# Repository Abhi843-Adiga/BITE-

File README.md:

Bite Force Measurement Device:  
A project for a portable, ESP32-based device designed to measure bite force, intended for wellness and bio-feedback applications.

Project Overview : 

->This open-source project provides the hardware foundation for a handheld device that measures bite force using a Flexiforce sensor.   
->The data is processed by an ESP32-C3 MCU and displayed in real-time on an SPI screen.  
->The device is designed to be a portable, battery-powered,rechargable tool for non-medical, wellness-related bio-feedback and personal data tracking.

Firmware:

This repository contains the hardware design only. The firmware needs to be developed separately using platforms like the ESP-IDF or the Arduino Core for ESP32.

Core firmware tasks would include:
1.  Reading analog values from the Flexiforce sensor via the MCP6004.
2.  Converting ADC values to force units (Newtons or lbs).
3.  Driving the SPI display to show real-time readings.

Design & Development Disclaimer:

1.Hardware Status:
These PCB designs are for prototyping purposes only.
Passed Checks:
The layouts have passed basic ERC (Electrical Rules Check) and DRC (Design Rule Check).

Untested Aspects:
The designs have not been validated for Signal Integrity (SI),Power Integrity (PI), or EMI/EMC.

They are not guaranteed to pass regulatory certifications without further analysis and revisions.

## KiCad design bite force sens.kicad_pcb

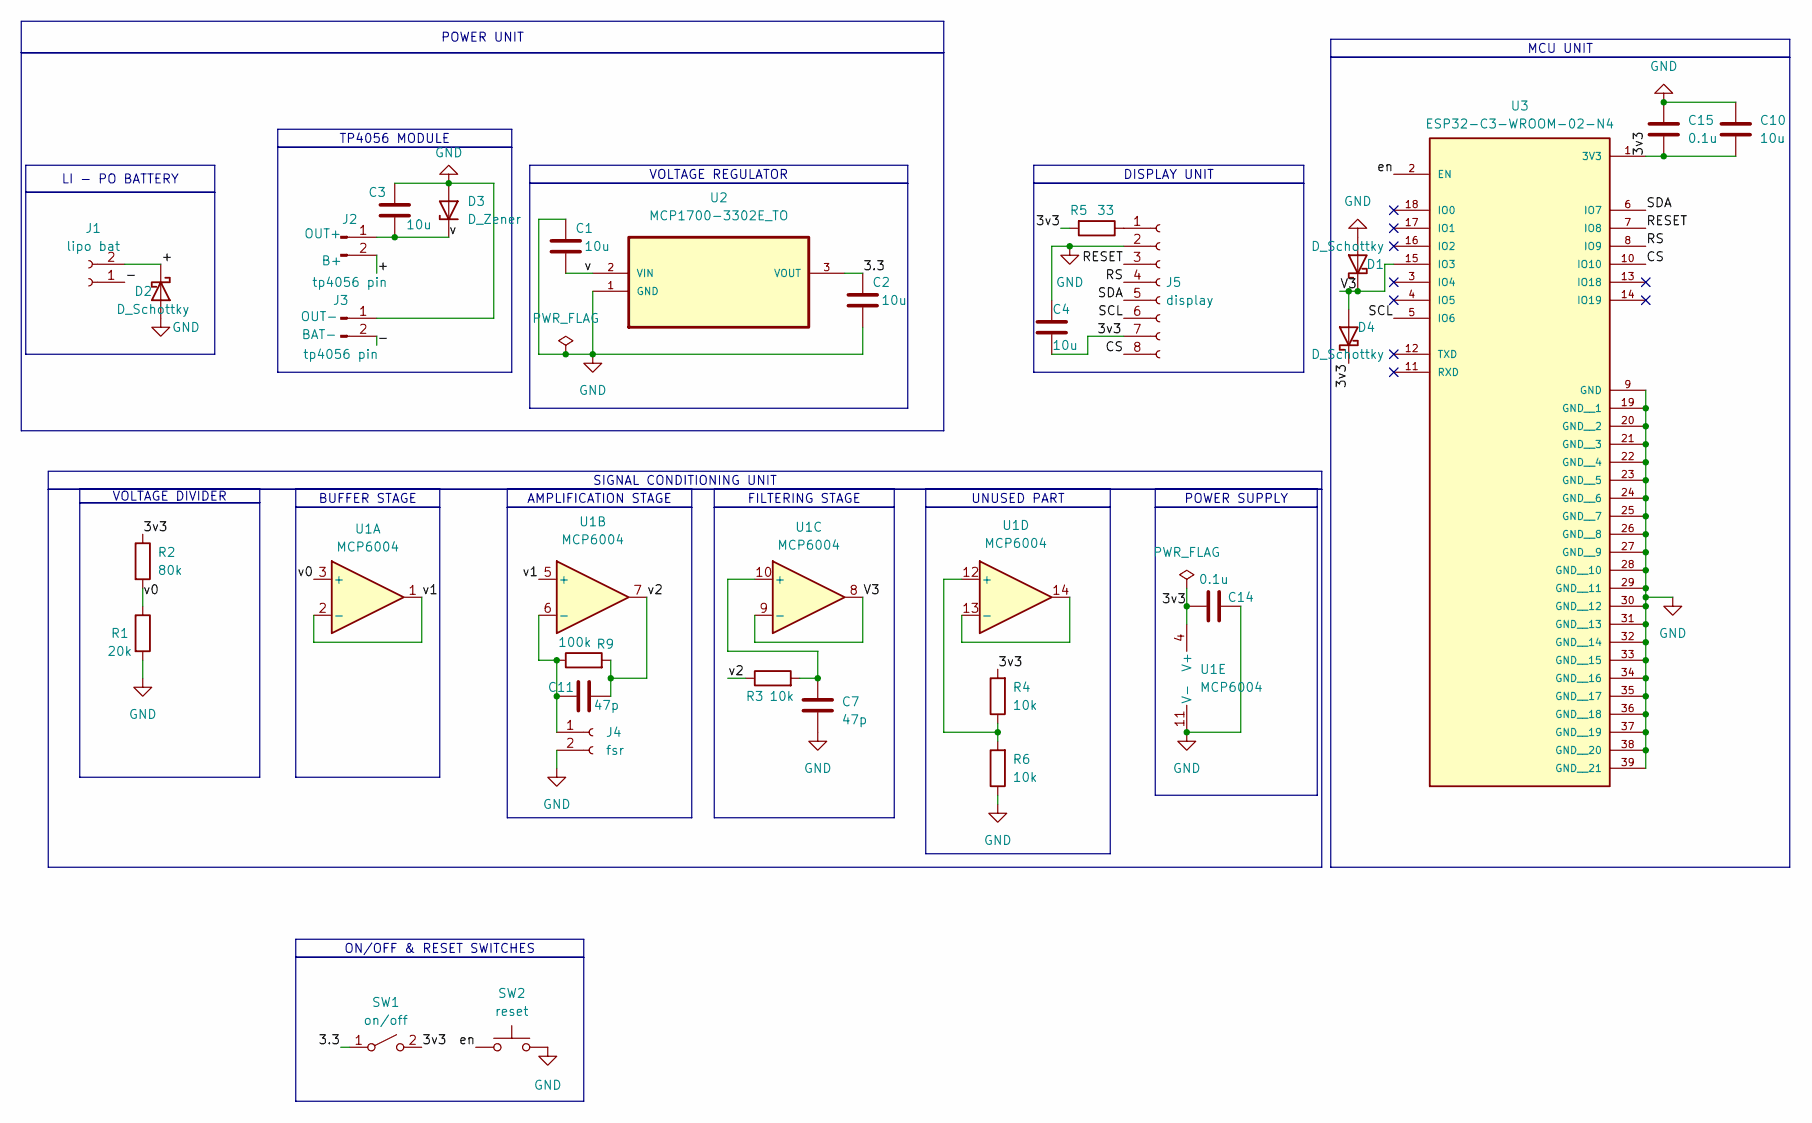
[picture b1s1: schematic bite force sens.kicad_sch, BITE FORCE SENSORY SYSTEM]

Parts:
C1, C2, C3, C4, C10: 10u; C_0805_2012Metric
C7, C11: 47p; C_0805_2012Metric
C14, C15: 0.1u; C_0805_2012Metric
D1, D2, D4: D_Schottky; D_SMA
D3: D_Zener; D_SMA
J1: lipo bat; JWT_A3963_1x02_P3.96mm_Vertical
J2, J3: tp4056 pin; PinHeader_1x02_P2.54mm_Vertical
J4: fsr; JST_PH_B2B-PH-K_1x02_P2.00mm_Vertical
J5: display; Hirose_FH12-8S-0.5SH_1x08-1MP_P0.50mm_Horizontal
R1: 20k; R_0805_2012Metric
R2: 80k; R_0805_2012Metric
R3, R4, R6: 10k; R_0805_2012Metric
R5: 33; R_0805_2012Metric
R9: 100k; R_0805_2012Metric
SW1: on/off; SW_DIP_SPSTx01_Slide_6.7x4.1mm_W6.73mm_P2.54mm_LowProfile_J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
SW2: reset; SW_PUSH_6mm
U1: MCP6004; SOIC-14_3.9x8.7mm_P1.27mm
U2: MCP1700-3302E_TO; TO127P254X495-3; MPN MCP1700-3302E/TO
U3: ESP32-C3-WROOM-02-N4; MODULE_ESP32-C3-WROOM-02-H4

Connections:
/3.3: C2.1, SW1.1 (A), U2.3 (VOUT)
/3v3: C4.2, C10.2, C14.1, C15.2, D4.1 (K), J5.7, R2.1, R4.2, R5.2, SW1.2 (B), U1.4 (V+), U3.1 (3V3)
/+: D2.1 (K), J1.2, J2.2
/-: J1.1, J3.2
/CS: J5.8, U3.10 (IO10)
/RESET: J5.3, U3.7 (IO8)
/RS: J5.4, U3.8 (IO9)
/SCL: J5.6, U3.5 (IO6)
/SDA: J5.5, U3.6 (IO7)
/V3: D1.1 (K), D4.2 (A), U1.8, U1.9 (-), U3.15 (IO3)
/en: SW2.1, U3.2 (EN)
/v: C1.2, C3.2, D3.1 (K), J2.1, U2.2 (VIN)
/v0: R1.1, R2.2, U1.3 (+)
/v1: U1.1, U1.2 (-), U1.5 (+)
/v2: C11.2, R3.1, R9.2, U1.7
GND: C1.1, C2.2, C3.1, C4.1, C7.2, C10.1, C14.2, C15.1, D1.2 (A), D2.2 (A), D3.2 (A), J3.1, J4.2, J5.2, R1.2, R6.1, SW2.2, U1.11 (V-), U2.1 (GND), U3.9 (GND), U3.19 (GND__1), U3.20 (GND__2), U3.21 (GND__3), U3.22 (GND__4), U3.23 (GND__5), U3.24 (GND__6), U3.25 (GND__7), U3.26 (GND__8), U3.27 (GND__9), U3.28 (GND__10), U3.29 (GND__11), U3.30 (GND__12), U3.31 (GND__13), U3.32 (GND__14), U3.33 (GND__15), U3.34 (GND__16), U3.35 (GND__17), U3.36 (GND__18), U3.37 (GND__19), U3.38 (GND__20), U3.39 (GND__21)
unnamed: C11.1, J4.1, R9.1, U1.6 (-)
unnamed: J5.1, R5.1
unnamed: C7.1, R3.2, U1.10 (+)
unnamed: R4.1, R6.2, U1.12 (+)
unnamed: U1.13 (-), U1.14

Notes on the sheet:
LI - PO BATTERY
POWER UNIT
MCU UNIT
TP4056 MODULE
UNUSED PART
FILTERING STAGE
DISPLAY UNIT
SIGNAL CONDITIONING UNIT
VOLTAGE REGULATOR
VOLTAGE DIVIDER
ON/OFF & RESET SWITCHES
POWER SUPPLY
BUFFER STAGE
AMPLIFICATION STAGE

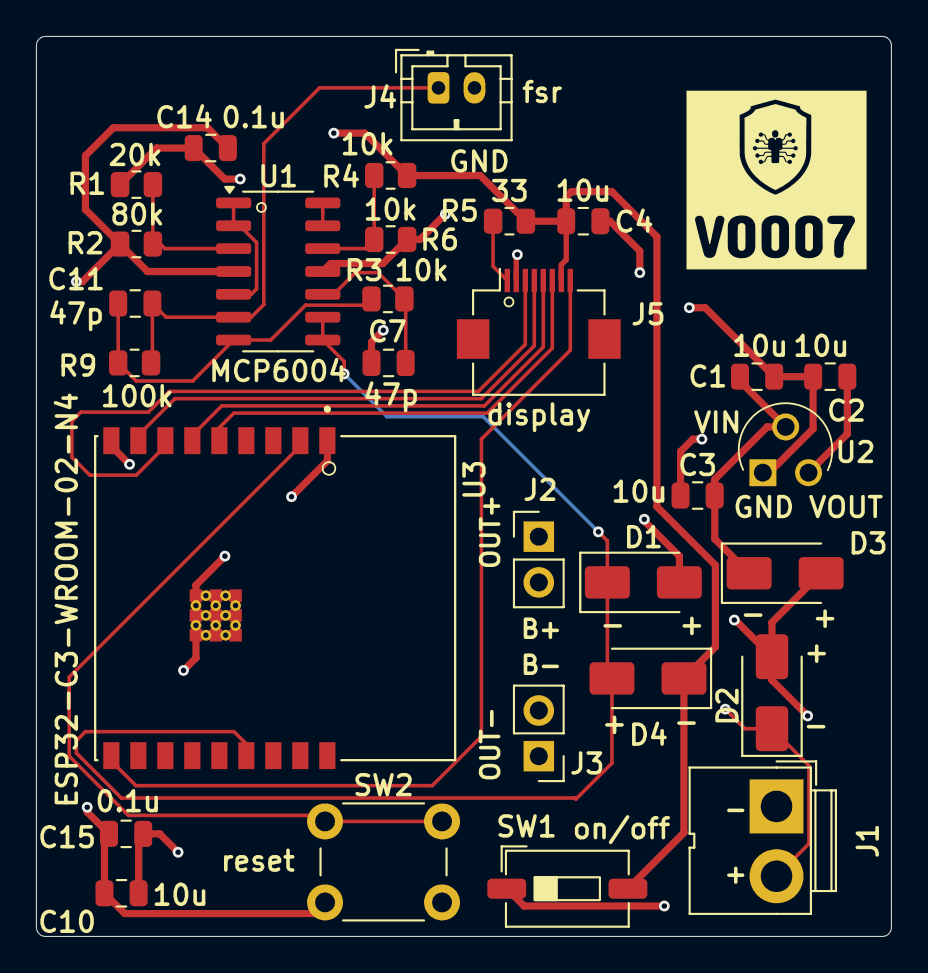
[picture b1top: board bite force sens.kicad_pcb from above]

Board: 4 copper layers, 47.5 x 50.0 mm, 30 parts (0 on the bottom side), 21 nets.

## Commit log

2025-06-18 added ressitor
2025-06-18 added ressitor again
2025-06-18 removed un
2025-06-24 bite force sensor sample is completed start of fine tuning after this
2025-06-25 made entire change in design and now the fresh pcb will be done and comitted at next commit
2025-06-27 completed the pcb design
2025-06-27 plotted some gerber files
2025-07-09 Changed the pcb to 4layer since the mcu is used and this is just the model without looking for the SI/PI,EMC/EMI
